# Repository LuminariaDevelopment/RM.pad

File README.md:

# RM.pad
A mechanical macropad designed for productivity and musical expression with a minimalistic and clean design.

## Features
* Three Layers: Productivity, System/Media, and a bonus mini MIDI Instrument.
* Layer-Specific Lighting: Visual feedback that changes depening on which layer you are currently using.
* Multi-Function Rotary Encoder: Context-aware knob for volume, scrolling, and MIDI CC.

## Usage

The RM.pad uses a layer system. Navigation and feedback are handled via the bottom-left key and the integrated NeoPixels.

### Layer Navigation
* **Switching Layers:** Press the bottom-left key to cycle through modes!
* **Visual Indicators:**
    * Deep Blue: Layer 0 (Productivity focused)
    * Sky Blue: Layer 1 (System focused)
    * White: Layer 2 (MIDI)

### Layer 0: Productivity (Deep Blue)
Designed for Windows OS and browser navigation.
* **Top Row:** Open Run Command (Win+R), New Tab (Ctrl+T), Focus Address Bar (Ctrl+L).
* **Middle Row:** Show Desktop (Win+D), Close Window (Alt+F4), Maximize Window (Win+Up).
* **Bottom Row:** Cycle Layer, Text Macro (Pre-defined sentence), Lock PC (Win+L).
* **Encoder:** Rotate for Volume Up/Down; Press to Mute.

### Layer 1: System and Media (Sky Blue)
Designed for media playback and hardware settings.
* **Top Row:** Play/Pause, Next Track, Previous Track.
* **Middle Row:** Toggle RGB Power, Cycle RGB Animations, Reset to Static Sky Blue.
* **Bottom Row:** Cycle Layer, No Command (for now), Reset Microcontroller.
* **Encoder:** Rotate for Page Up/Down; Press for Home key.

### Layer 2: MIDI Keyboard (White)
Turns the macropad into a musical instrument for DAWs or web synths.
* **Keypad:** 8 keys mapped to the C-Major scale (C, D, E, F, G, A, B, C).
* **Bottom-Left Key:** Cycles back to Layer 0.
* **Encoder:** Rotate to send MIDI CC (Continuous Controller) data for like volume or filter cutoff.

### MIDI Integration
To use the MIDI layer, simply open your Digital Audio Workstation (DAW) and select "KMK MIDI" as the active MIDI Input device.

# Bill Of Materials

XIAO RP2040 Microcontroller - [here](https://www.amazon.in/Microcontroller-Dual-Core-MicroPython-CircuitPython-Interfaces/dp/B09NNVNW7M/ref=sr_1_1_sspa?nsdOptOutParam=true&sr=8-1-spons&sp_csd=d2lkZ2V0TmFtZT1zcF9hdGY&psc=1) (x1)

1N4148 / Diodes - [here](https://www.digikey.com/en/products/detail/onsemi/1N4148/458603) (x9)

Cherry MX Keys - [here](https://www.amazon.in/dp/B09ZT8BY6W/ref=twister_B0BFGC2MJY?_encoding=UTF8) (x9)

SK6812 Mini - [here](https://keeb.io/products/sk-6812-mini-e-rgb-leds-12-pack) (x3)

EC11 Rotary Encoder - [here](https://keeb.io/products/rotary-encoder-ec11) (x1)

1.7mm(diameter)x10mm screws (x4)  - [here](https://www.moddiy.com/products/M1.7-x-10mm-Black-Screws-(PM1.7X10).html)

Blank DSA Keycaps (Black)(x9) - [here](https://meckeys.com/shop/accessories/keyboard-accessories/keycaps/blank-dsa-keycaps-1u/)

(AI was used to polish `README.md` for better readability)

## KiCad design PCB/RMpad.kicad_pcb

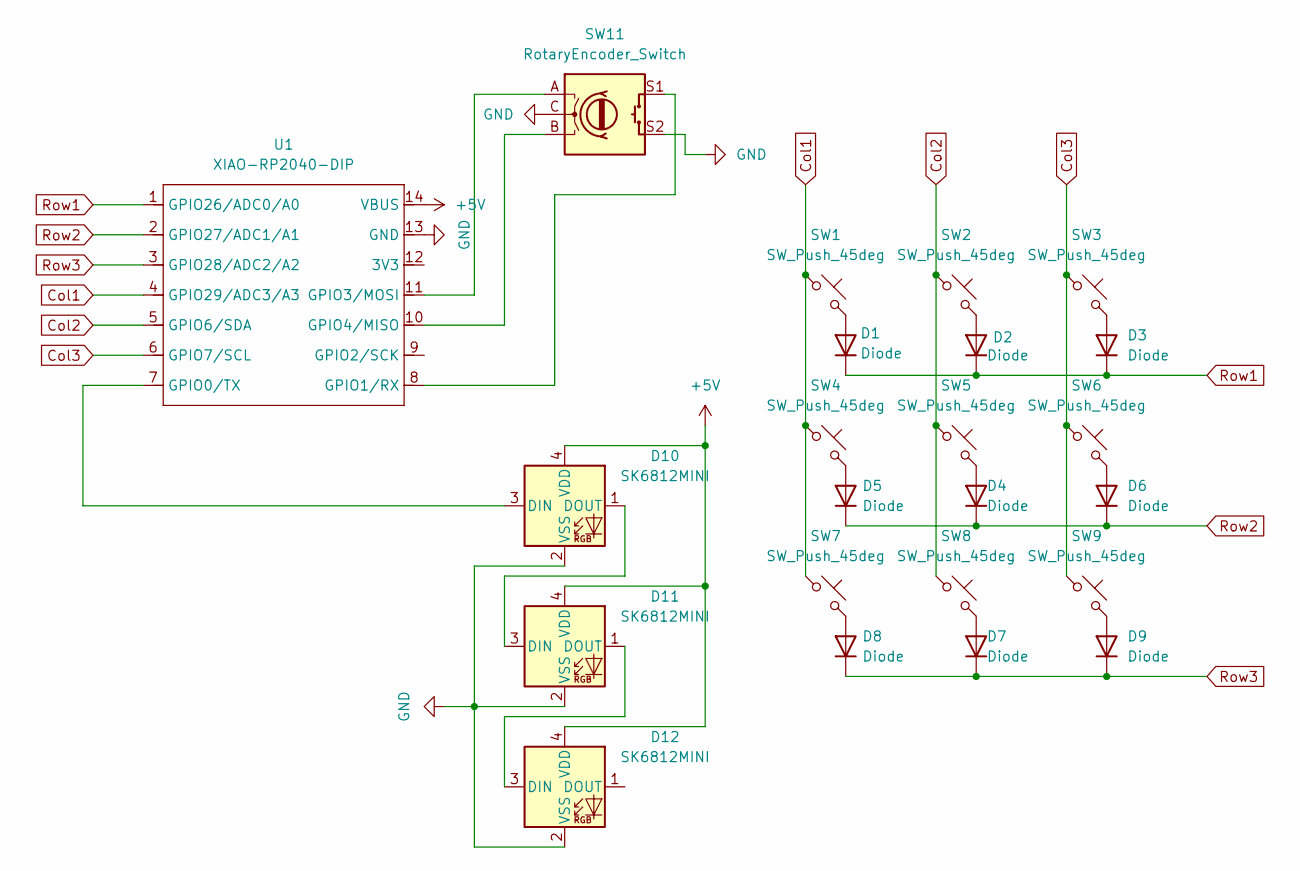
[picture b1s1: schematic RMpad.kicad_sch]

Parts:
D1, D2, D3, D4, D5, D6, D7, D8, D9: Diode; Diode_DO-35
D10, D11, D12: SK6812MINI; LED_SK6812MINI_PLCC4_3.5x3.5mm_P1.75mm
SW1, SW2, SW3, SW4, SW5, SW6, SW7, SW8, SW9: SW_Push_45deg; SW_Cherry_MX_1.00u_PCB
SW11: RotaryEncoder_Switch; RotaryEncoder_Alps_EC11E-Switch_Vertical_H20mm_CircularMoun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
U1: XIAO-RP2040-DIP

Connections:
+5V: D10.4 (VDD), D11.4 (VDD), D12.4 (VDD), U1.14 (VBUS)
Col1: SW1.1, SW4.1, SW7.1, U1.4 (GPIO29/ADC3/A3)
Col2: SW2.1, SW5.1, SW8.1, U1.5 (GPIO6/SDA)
Col3: SW3.1, SW6.1, SW9.1, U1.6 (GPIO7/SCL)
GND: D10.2 (VSS), D11.2 (VSS), D12.2 (VSS), SW11.C, SW11.S2, U1.13 (GND)
unnamed: D1.2 (A), SW1.2
unnamed: D2.2 (A), SW2.2
unnamed: D3.2 (A), SW3.2
unnamed: D4.2 (A), SW4.2
unnamed: D5.2 (A), SW5.2
unnamed: D6.2 (A), SW6.2
unnamed: D7.2 (A), SW7.2
unnamed: D8.2 (A), SW8.2
unnamed: D9.2 (A), SW9.2
unnamed: D10.3 (DIN), U1.7 (GPIO0/TX)
unnamed: D10.1 (DOUT), D11.3 (DIN)
unnamed: D11.1 (DOUT), D12.3 (DIN)
unnamed: SW11.S1, U1.8 (GPIO1/RX)
unnamed: SW11.A, U1.11 (GPIO3/MOSI)
unnamed: SW11.B, U1.10 (GPIO4/MISO)
Row1: D1.1 (K), D2.1 (K), D3.1 (K), U1.1 (GPIO26/ADC0/A0)
Row2: D4.1 (K), D5.1 (K), D6.1 (K), U1.2 (GPIO27/ADC1/A1)
Row3: D7.1 (K), D8.1 (K), D9.1 (K), U1.3 (GPIO28/ADC2/A2)

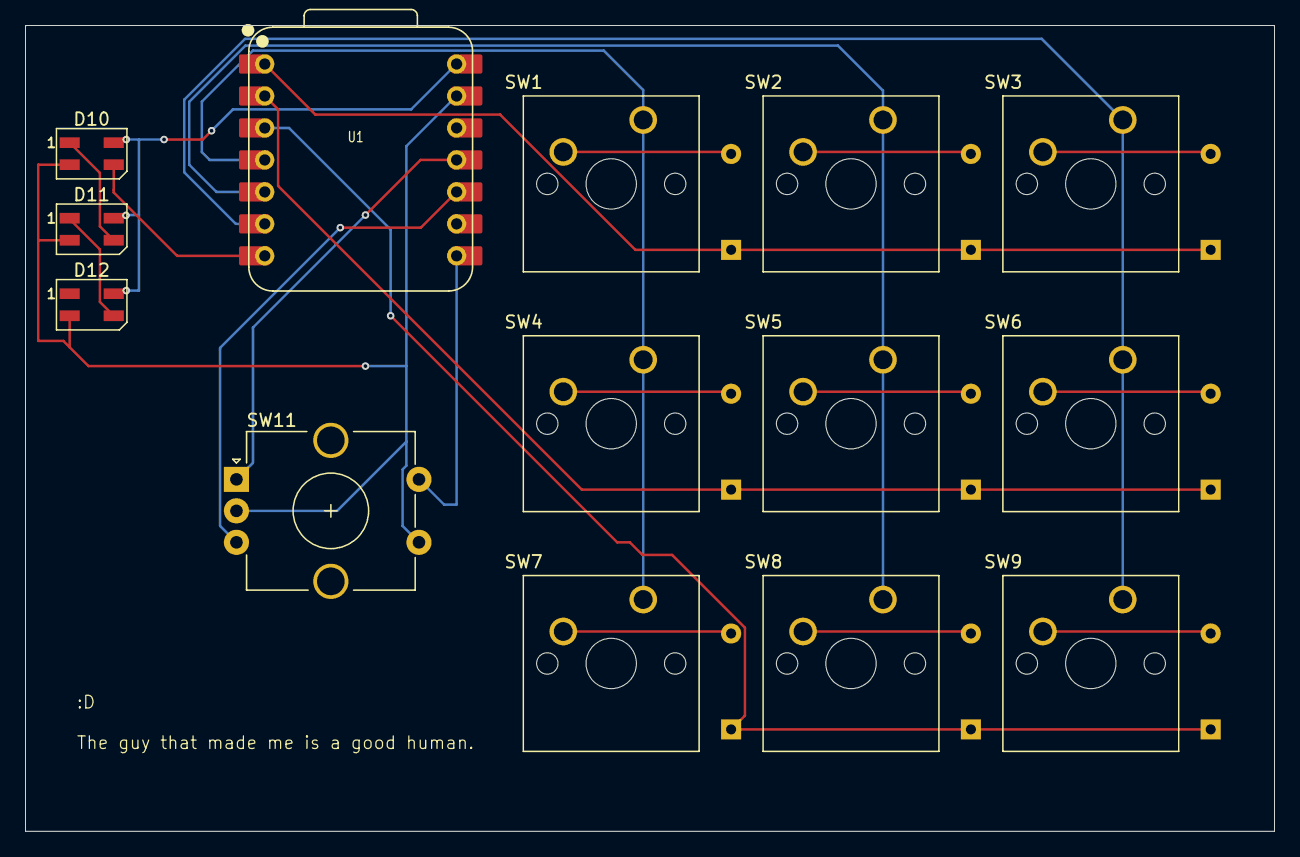
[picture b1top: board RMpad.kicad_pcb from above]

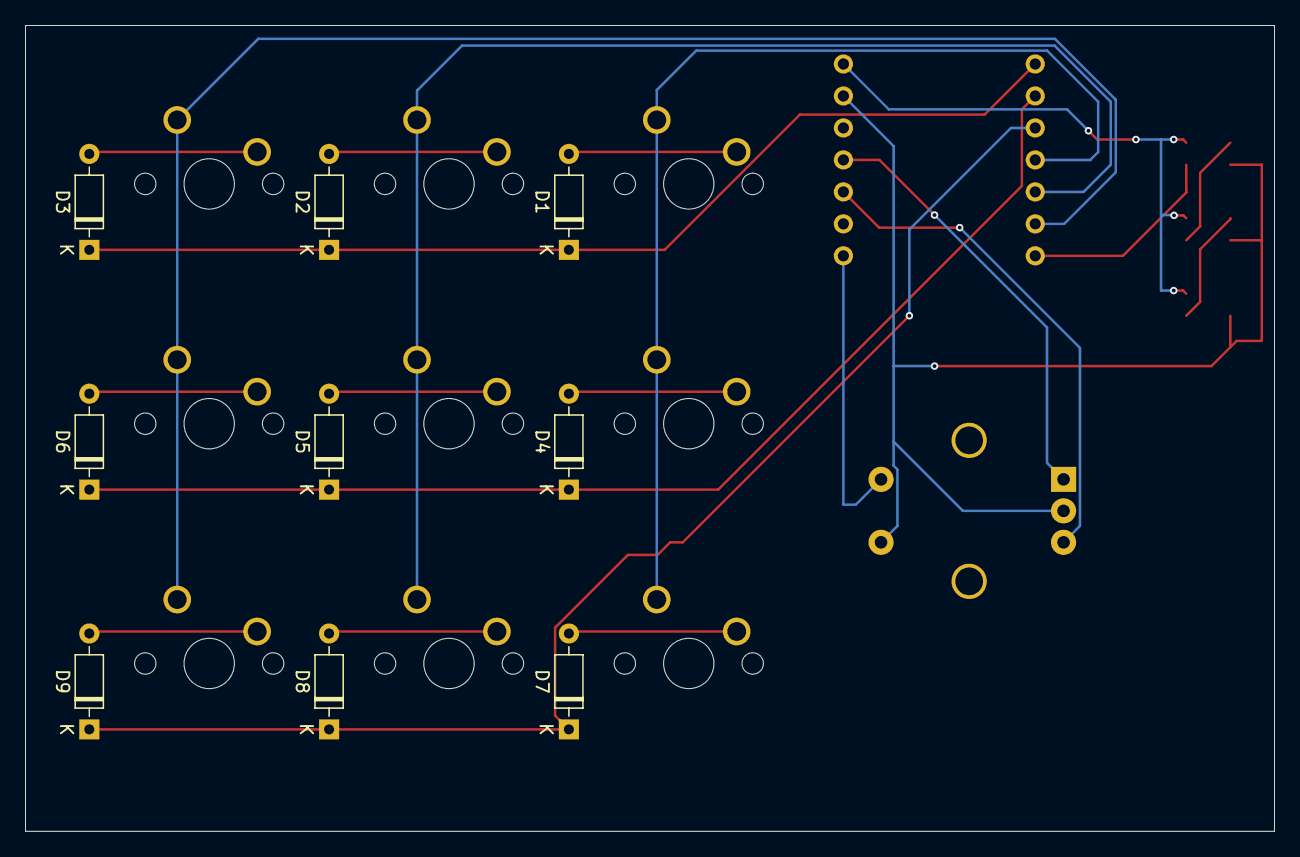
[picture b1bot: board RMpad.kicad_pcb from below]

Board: 2 copper layers, 99.2 x 64.0 mm, 23 parts (9 on the bottom side), 23 nets.

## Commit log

2026-02-07 pcb export and main.py
2026-02-07 stl exports
2026-02-08 step export
2026-02-10 gerber zipping
